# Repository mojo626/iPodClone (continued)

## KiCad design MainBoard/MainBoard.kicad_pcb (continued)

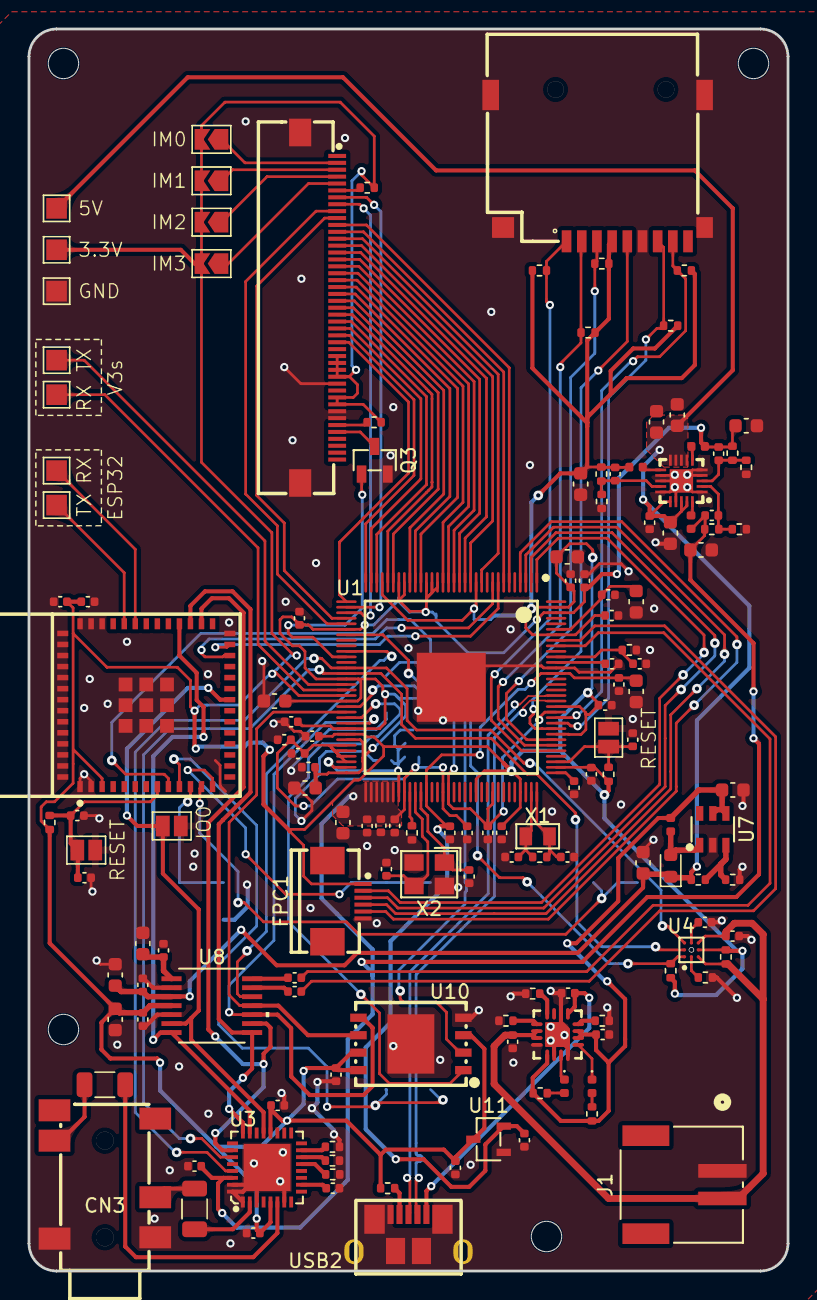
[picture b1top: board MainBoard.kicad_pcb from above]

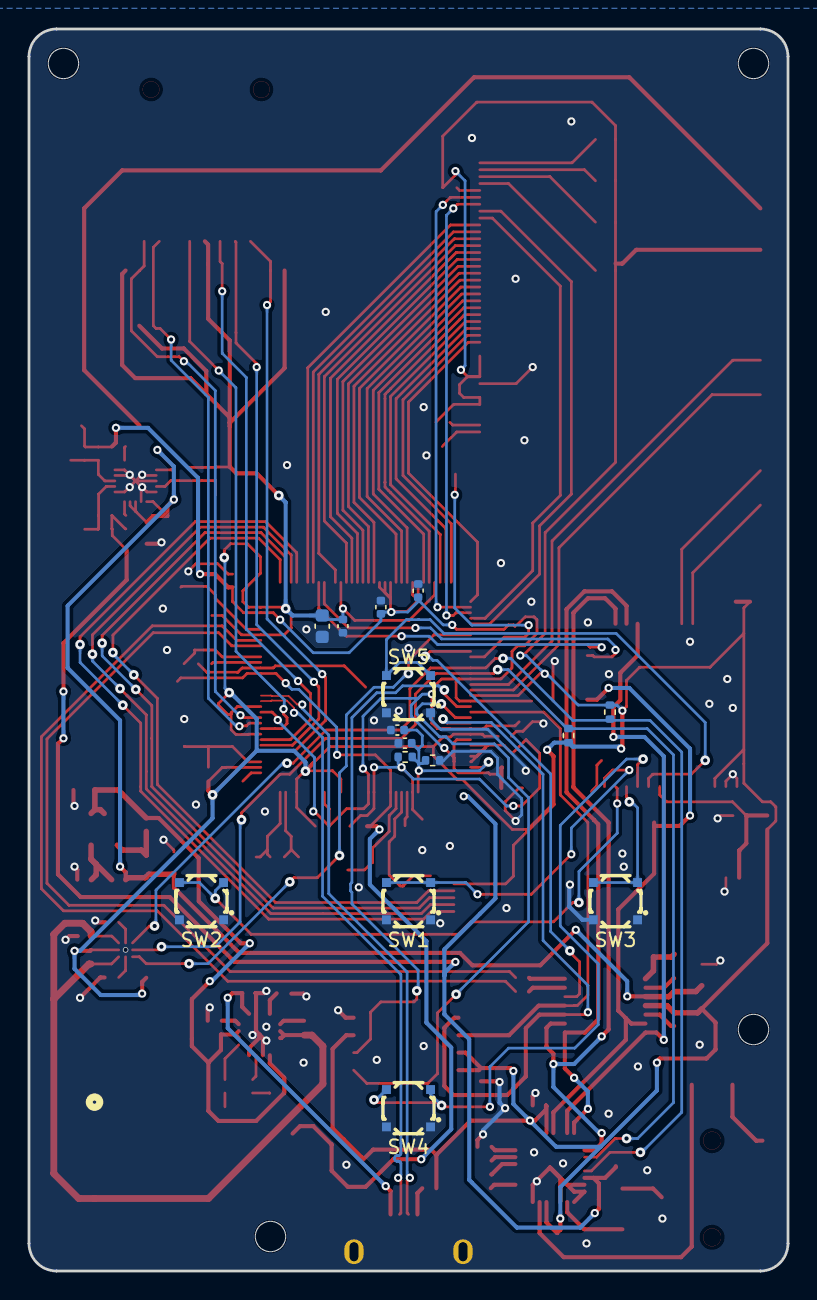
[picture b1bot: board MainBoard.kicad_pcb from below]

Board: 2 copper layers, 55.0 x 90.0 mm, 163 parts (15 on the bottom side), 117 nets.

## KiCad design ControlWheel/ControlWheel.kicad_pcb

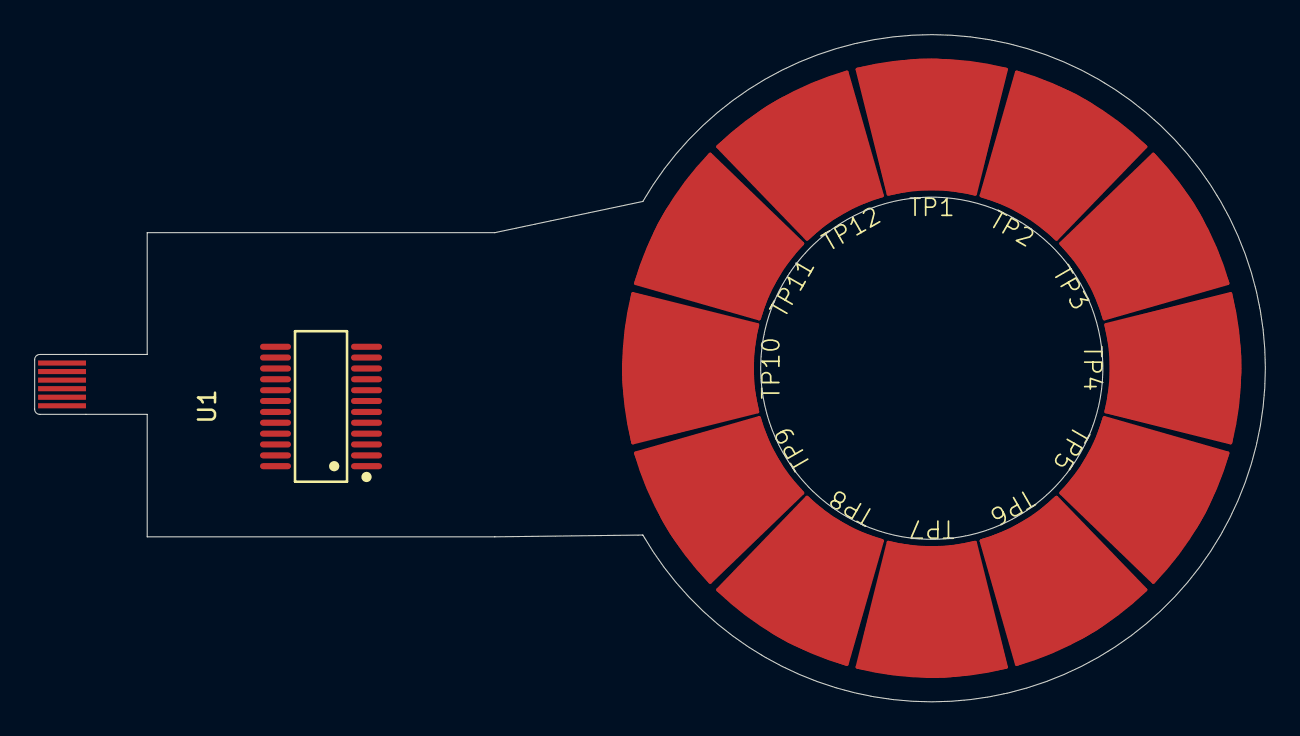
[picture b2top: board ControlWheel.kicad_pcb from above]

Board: 2 copper layers, 71.9 x 39.0 mm, 14 parts (0 on the bottom side), 7 nets, no tracks yet.

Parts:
J1: Conn_01x06_Pin; 6pin_0.5mm-Pitch
TP1, TP2, TP3, TP4, TP5, TP6, TP7, TP8, TP9, TP10, TP11, TP12: TestPoint; RoundPad
U1: AI12; SSOP-24_L8.8-W4.0-P0.64-LS6.2-BL

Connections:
+3.3V: J1.6, U1.19 (VDD)
/BCD0: J1.5, U1.16 (BCD0)
/BCD1: J1.4, U1.15 (BCD1)
/BCD2: J1.3, U1.14 (BCD2)
/BCD3: J1.2, U1.13 (BCD3)
GND: J1.1, U1.21 (GND)
unnamed: U1.17 (S2), U1.18 (S2)

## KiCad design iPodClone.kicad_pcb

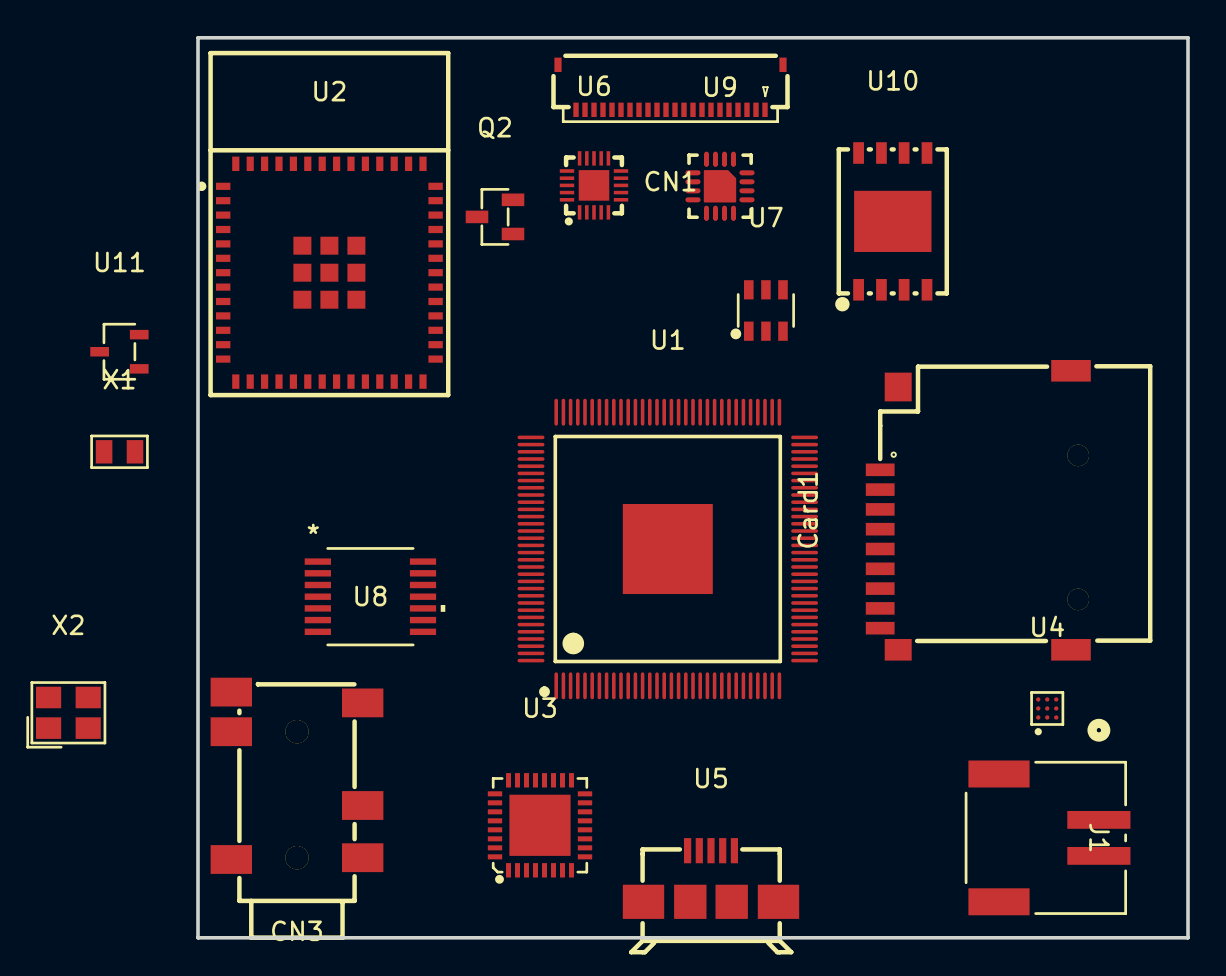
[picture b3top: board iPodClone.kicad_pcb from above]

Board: 2 copper layers, 55.0 x 50.0 mm, 18 parts (0 on the bottom side), 39 nets, no tracks yet.

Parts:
CN1: HC-FPC-05-09-22RLTAG; CONN-SMD_22P-P0.50_HCTL_HC-FPC-05-09-22RLTAG
CN3: PJ-342; AUDIO-SMD_PJ-342
Card1: TF PUSH; TF-SMD_TF-PUSH
J1: 1769; CONN_1769_ADA
Q2: MMBT2222ALT1G; SOT-23-3_L2.9-W1.3-P1.90-LS2.4-BR
U1: V3S; LQFP-128_L14.0-W14.0-P0.40-LS16.0-BL-EP5.0
U2: ESP32-MINI-1-H4; WIFI-SMD_ESP32-MINI-1
U3: SGTL5000XNAA3R2; QFN-32_L5.0-W5.0-P0.50-BL-EP3.4
U4: BQ27220YZFR; DSBGA-9_L1.7-W1.6-R3-C3-P0.50-BL
U5: 10104110-0001LF; MICRO-USB-SMD_AMPHENOL_10104110-0001LF
U6: EA3036C; WQFN-20_L3.0-W3.0-P0.40-BL-EP
U7: MT3608; SOT-23-6_L2.9-W1.6-P0.95-LS2.8-BL
U8: PCM1807PW; PW14
U9: BQ24074RGTR; QFN-16_L3.0-W3.0-P0.50-TL-EP1.7
U10: F35SQA512M-WWT; WSON-8_L8.0-W6.0-P1.27-BL-EP-1
U11: XC6206P302MR_C5148691; SOT-23-3_L3.0-W1.7-P0.95-LS2.9-BR
X1: FC-12M32.768KHZ7PF20PPM; FC-12M_L2.0-W1.2
X2: X322524MOB4SI; CRYSTAL-SMD_4P-L3.2-W2.5-BL

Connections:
+1V2: U1.19 (VDD-SYS3), U1.20 (VDD-CPU3), U1.21 (VDD-CPU2), U1.25 (VDD-CPU1), U1.26 (VDD-CPU0), U1.38 (VDD-CPU4), U1.51 (VDD-CPU6), U1.56 (VDD-CPU7), U1.58 (VDD-SYS4), U1.64 (VDD-SYS5), U1.80 (VDD-SYS0), U1.88 (EPHY-VDD), U1.108 (VDD-SYS1), U1.126 (VDD-SYS2)
+1V8: U1.59 (VCC-DRAM8), U1.60 (VCC-DRAM9), U1.61 (VCC-DRAM10), U1.62 (VCC-DARM11), U1.65 (VCC-DRAM0), U1.66 (VCC-DRAM1), U1.67 (VCC-DRAM2), U1.68 (VCC-DRAM3), U1.69 (VCC-DRAM4), U1.70 (VCC-DRAM5), U1.72 (VCC-DRAM6), U1.79 (VCC-DRAM7), U3.30 (VDDD)
+3.3V: CN1.1 (A), CN1.3 (IM2), CN1.4 (IM1), CN1.6 (VCI), Card1.4 (VDD), U1.12 (VCC-PE0), U1.29 (VCC-PE1), U1.50 (VCC-IO3), U1.57 (VCC-IO2), U1.85 (VCC-MCSI), U1.93 (EPHY-VCC), U1.98 (VCC-RTC), U1.104 (VCC-IO0), U1.109 (VCC-USB), U1.122 (HPVCCIN), U1.127 (VCC-IO1), U2.3 (3V3), U3.5 (VDDA), U3.20 (VDDIO), U4.C2 (SRN), U8.4 (VDD), U10.3 (~WP/SIO2), U10.7 (~HOLD/SIO3), U10.8 (VCC), U11.3 (VIN)
+3V0: U1.76 (VCC-PLL), U1.115 (AVCC), U11.2 (VOUT)
+5V: U6.7 (VIN2), U6.8 (EN2), U6.9 (EN1), U6.10 (VIN1), U6.16 (VCC), U6.18 (EN3), U6.19 (VIN3), U8.3 (VCC)
+VBAT: J1.2, U4.C1 (SRP), U4.C3 (BAT), U9.2 (BAT), U9.3 (BAT)
/SVREF: U1.63 (SVREF1), U1.71 (SVREF0)
/USB_D+: U1.111 (USB-DP), U5.3 (D+)
/USB_D-: U1.110 (USB-DM), U5.2 (D-)
/X24MIN: U1.75 (X24MIN), X2.1 (OSC1)
/X24MOUT: U1.74 (X24MOUT), X2.3 (OSC2)
/X32KIN: U1.96 (X32KIN), X1.1 (OSC1)
/X32KOUT: U1.95 (X32KOUT), X1.2 (OSC2)
GND: CN1.5 (IM0), CN1.7 (DB7), CN1.8 (DB6), CN1.9 (DB5), CN1.10 (DB4), CN1.11 (DB3), CN1.12 (DB2), CN1.13 (DB1), CN1.14 (DB0), CN1.15 (RD), CN1.22 (GND), CN1.23, CN1.24, Card1.6 (VSS), Card1.10, Card1.11, Card1.12, Card1.13, J1.1, Q2.2 (E), U1.116 (AGND), U1.129 (EGND), U2.1 (GND), U2.2 (GND), U2.27 (GND), U2.38 (GND), U2.39 (GND), U2.40 (GND), U2.41 (GND), U2.42 (GND), U2.43 (GND), U2.44 (GND), U2.45 (GND), U2.46 (GND), U2.47 (GND), U2.48 (GND), U2.49 (GND), U2.50 (GND), U2.51 (GND), U2.52 (GND), U2.53 (GND), U2.54 (GND), U2.55 (GND), U3.1 (GND), U3.3 (GND), U3.7 (AGND), U3.31 (CTRL_ADR0_CS), U3.32 (CTRL_MODE), U3.33 (GND), U4.B2 (VSS), U5.5 (GND), U5.6 (EH), U6.1 (GND3), U6.4 (GND2), U6.5 (GND2), U6.12 (GND1), U6.13 (GND1), U6.15 (AGND), U6.17 (AGND), U6.21 (PAD), U7.2 (GND), U8.2 (AGND), U8.5 (DGND), U9.4 (~CE), U9.6 (EN1), U9.8 (VSS), U9.14 (TMR), U9.17 (EP), U10.4 (GND), U10.9 (EP), U11.1 (VSS), X2.2 (GND), X2.4 (GND)
GPOUT: U1.35 (PE2/CSI_HSYNC/LCD_HSYNC), U4.A1 (GPOUT)
I2C_SCK: U1.45 (PB6/TWI0_SCK/PB_EINT6), U3.29 (CTRL_CLK), U4.A3 (SCL)
I2C_SDA: U1.46 (PB7/TWI0_SDA/PB_EINT7), U3.27 (CTRL_DATA), U4.A2 (SDA)
I2S_MCLK: U2.21 (IO0), U3.21 (SYS_MCLK), U8.6 (SCKI)
I2S_PCMOUT: U2.29 (IO5), U3.26 (I2S_DIN), U8.9 (DOUT)
I2S_SCK: U2.30 (IO18), U3.24 (I2S_SCLK), U8.8 (BCK)
I2S_WS: U2.31 (IO23), U3.23 (I2S_LRCLK), U8.7 (LRCK)
LCD_CS: CN1.18 (CS), U1.36 (PE1/CSI_MCLK/LCD_DE)
LCD_DC: CN1.16 (WR), U1.44 (PB5/PWM1/PB_EINT5)
LCD_LIGHT: Q2.1 (B), U1.43 (PB4/PWM0/PB_EINT4)
LCD_RST: CN1.20 (RST), U1.41 (PB2/UART2_RTS/PB_EINT2)
NAND_CS: U1.54 (PC2/SDC2_RST/SPI_CS), U10.1 (~CS)
unnamed: CN1.2 (K), Q2.3 (C)
PCM_CS: U1.37 (PE0/CSI_PCLK/LCD_CLK), U8.12 (MS)
SDC0_CLK: Card1.5 (CLX), U1.105 (PF2/SDC0_CLK/UART0_TX)
SDC0_CMD: Card1.3 (CMD), U1.103 (PF3/SDC0_CMD/JTAG_DO1)
SDC0_D0: Card1.7 (DAT0), U1.106 (PF1/SDC0_D0/JTAG_DI1)
SDC0_D1: Card1.8 (DAT1), U1.107 (PF0/SDC0_D1/JTAG_MS1)
SDC0_D2: Card1.1 (DAT2), U1.101 (F5/SDC0_D2/JTAG_CK1)
SDC0_D3: Card1.2 (CD/DAT3), U1.102 (PF4/SDC0_D3/UART0_RX)
SPI_CLK: CN1.17 (RS), U1.53 (PC1/SDC2_CMD/SPI_CLK), U8.11 (MC), U10.6 (CLK)
SPI_MISO: U1.52 (PC0/SDC2_CLK/SPI_MISO), U10.2 (DO/SIO1)
SPI_MOSI: CN1.21 (SDA), U1.55 (PC3/SDC2_D0/SPI_MOSI), U8.10 (MD), U10.5 (DI/SIO0)
VBUS: U5.1 (VCC), U9.13 (IN)
VSYS: U7.5 (IN), U9.5 (EN2), U9.10 (OUT), U9.11 (OUT)

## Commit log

2025-05-09 starting
2025-05-10 power changes, audio changes, testing layout
2025-05-10 audio changes, better layout
2025-05-10 before switching to ESP32 module
2025-05-10 start of adding esp32 module
2025-05-11 power changes to v3s, nand
2025-05-11 power changes for v3s, cleanup
2025-05-11 gitignore and audio changes
2025-05-12 gitignore again
2025-05-12 changed file structure
2025-05-12 created control wheel PCB
2025-05-12 started control wheel
2025-05-12 footprints for wheel + power changes for v3s
2025-05-13 minor power changes
2025-05-16 layout and starting routing
2025-05-18 starting to route
2025-05-18 routed signals
2025-05-19 everything routed initial
2025-05-19 cleaned up silkscreen
2025-05-19 added teardrops and voltage probe points
2025-05-23 layout cleanup
2025-05-23 before moving esp32
2025-05-23 rotated ESP32
